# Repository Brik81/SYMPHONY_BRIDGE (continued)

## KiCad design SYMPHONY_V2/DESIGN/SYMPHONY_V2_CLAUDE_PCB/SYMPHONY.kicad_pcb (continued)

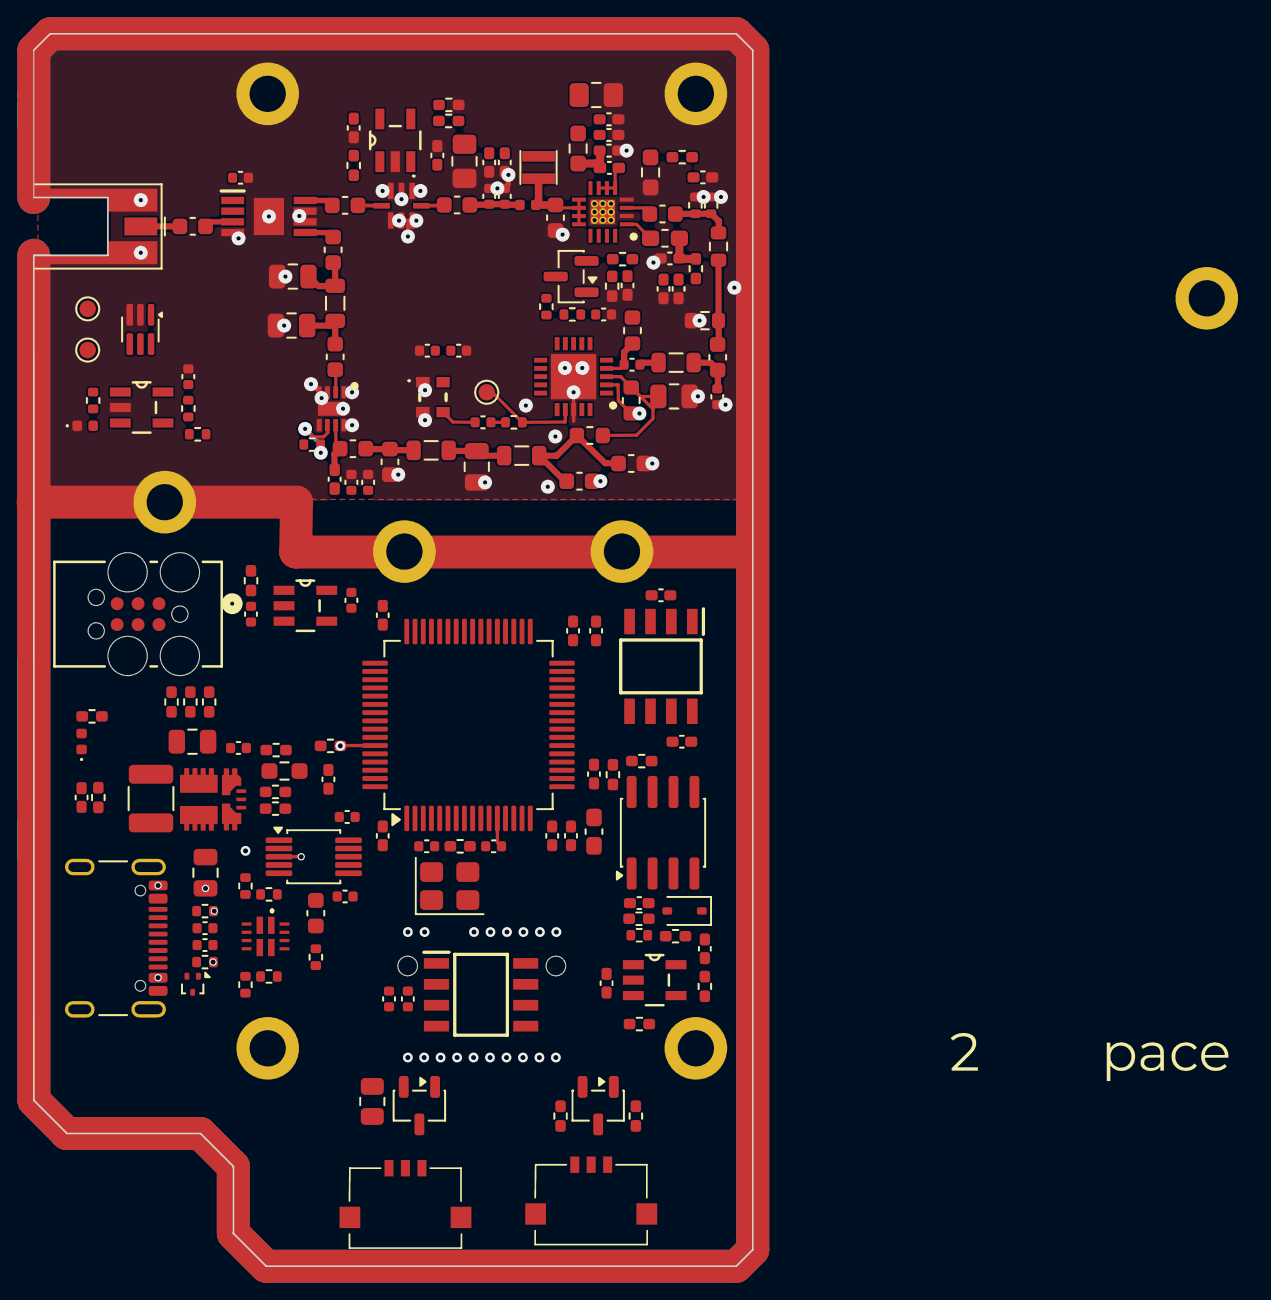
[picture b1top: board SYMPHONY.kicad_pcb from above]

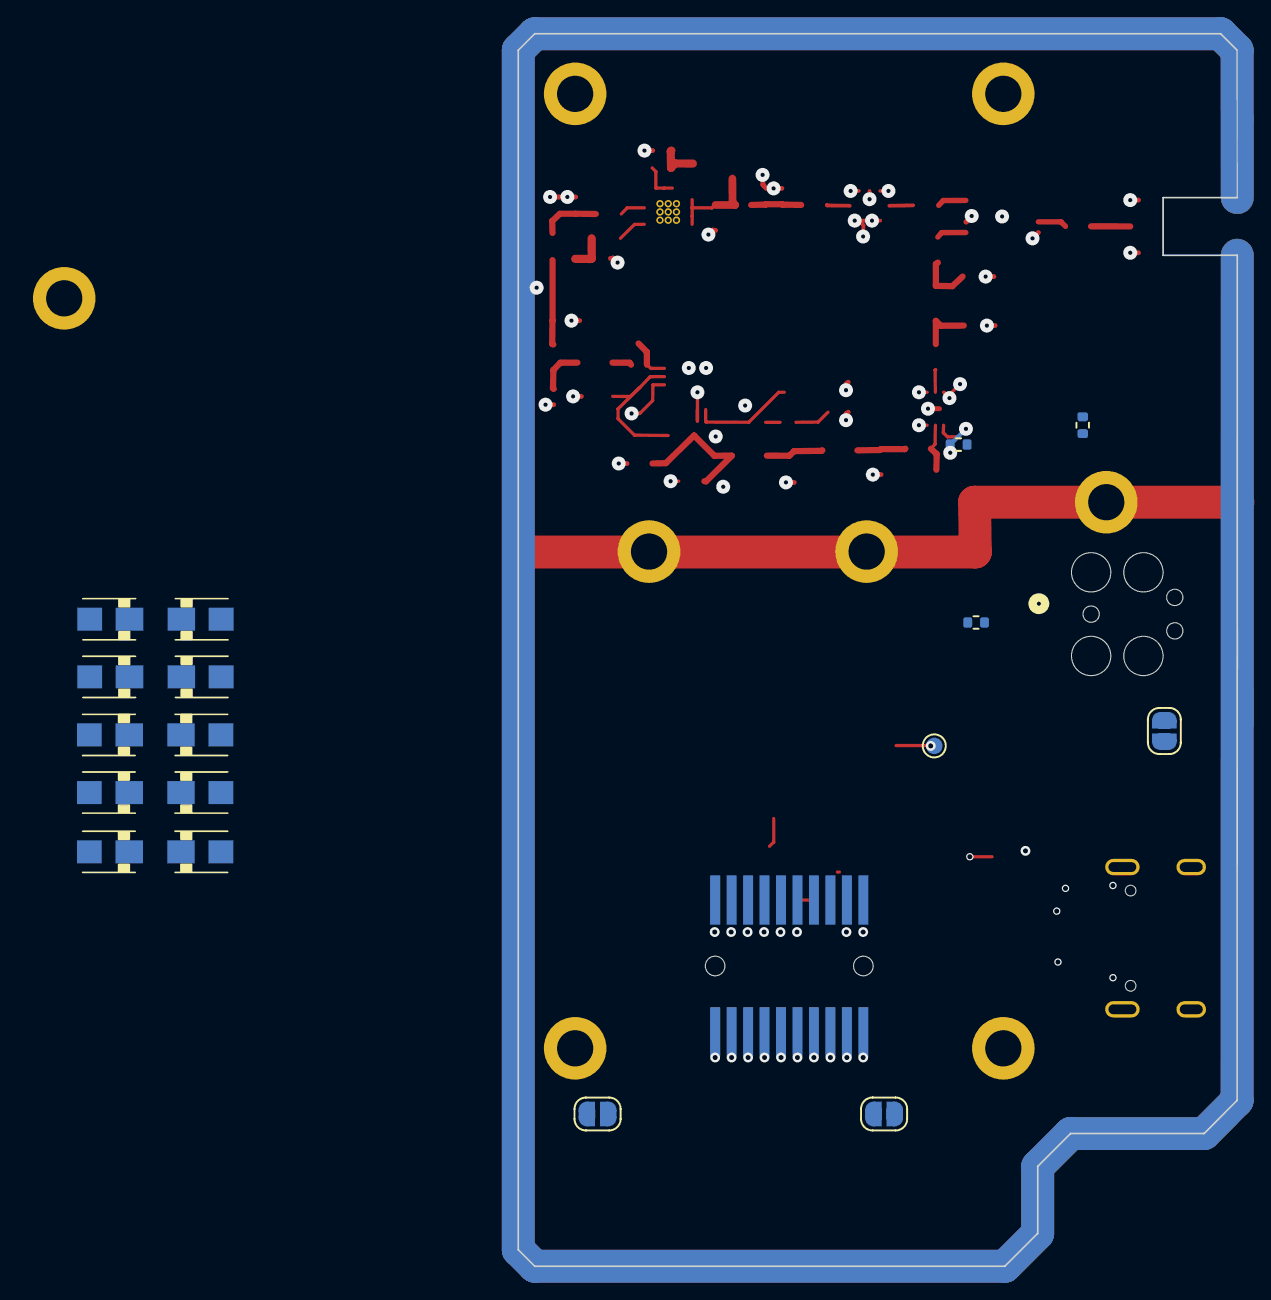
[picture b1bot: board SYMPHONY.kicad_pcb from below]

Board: 8 copper layers, 43.7 x 74.8 mm, 193 parts (18 on the bottom side), 108 nets.

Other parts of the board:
C419, C424: CPH3225A

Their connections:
GND: C419.2 (-), C424.2 (-); also elsewhere on the board
RTC_VBAT: C419.1 (+), C424.1 (+); also elsewhere on the board

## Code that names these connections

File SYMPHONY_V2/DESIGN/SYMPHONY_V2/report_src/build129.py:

import pathlib
d = pathlib.Path(__file__).parent
p = d / 'symphony_version_log.html'
h = p.read_text(encoding='utf8')

def sub1(o, rep):
    global h
    assert h.count(o) == 1, o[:60]
    h = h.replace(o, rep)


sub1('symphony_version_log · rev. 1.28"', 'symphony_version_log · rev. 1.29"')
sub1("<div><b>1.28</b> del 30/10/2026",
     "<div><b>1.29</b> del 02/11/2026 – R-04 chiuso senza modifiche allo schema: limite di potenza e sequenza TX affidati al firmware; raccolta delle note per il firmware (§41)</div><div>1.28 del 30/10/2026")
sub1('tr.r128 td {', 'tr.r129 td { background: #edf2e6 !important; }\ntr.r128 td {')
sub1('<li><a href="#partAA">Parte AA – Rev. 1.28: condensatori RF GQM1875 0603 (R-10) e decisione su J15 (R-09)</a></li>',
     '<li><a href="#partAA">Parte AA – Rev. 1.28: condensatori RF GQM1875 0603 (R-10) e decisione su J15 (R-09)</a></li>\n'
     '<li><a href="#partAB">Parte AB – Rev. 1.29: potenza TX (R-04) e note per il firmware</a></li>')
sub1('cipria</span> = rev. 1.28,',
     'cipria</span> = rev. 1.28, righe <span style="background:#edf2e6;padding:0 2mm">salvia</span> = rev. 1.29,')

REV = ('<tr class="r129"><td>1.29</td><td>problema R-04 della revisione indipendente del 27/10/2026<br>decisione di Brik81 del 02/11, registrata da Claude Code</td>'
       '<td>Nessuna modifica allo schema. Il limite della potenza in uscita (≤ 31 dBm all\'antenna) e la sequenza di trasmissione sono requisiti del firmware; misura obbligatoria sul prototipo; R242/R243 restano come regolazione della VAPC. Aggiunta la raccolta delle note per il firmware (§41)</td>'
       '<td>Claude Code</td><td><b>Brik81</b></td>'
       '<td>"si se l\'hw è corretto andiamo di A e lasciamo scritto al firmwarsita" (02/11)</td></tr>\n')
i = h.find('<h2>Registro revisioni</h2>'); j = h.find('</table>', i); h = h[:j] + REV + h[j:]
sub1('Rev. 1.28: <code>UHF.kicad_sch</code>',
     'Rev. 1.29: nessun file di progetto modificato. Rev. 1.28: <code>UHF.kicad_sch</code>')

rows = ('<tr class="r129"><td>1.29-01</td><td>UHF</td><td>Catena TX (IC204 → pad → IC2 → FL201 → IC202)</td>'
        '<td>Con il Si4464 a +20 dBm il PA è in saturazione profonda (≈ +9 dBm in ingresso, ne bastano ≈ −9). Al commutatore arrivano ≈ 32,5 dBm, contro un massimo assoluto dell\'HMC349 di 33,5 dBm (30 dBm in hot switching); l\'LFCG-490+ a 85 °C regge ≈ 1,9 W</td>'
        '<td>Nessuna modifica all\'hardware. Requisiti firmware F-01 e F-02 (§41) e misura M-01 sul prototipo. Se Pout supera i 31 dBm anche con il limite firmware, si ritoccano R242/R243</td>'
        '<td>R-04, §41</td><td>Brik81 · 02/11</td><td>—</td></tr>\n')
i = h.find('<h2>Registro modifiche</h2>'); j = h.find('</table>', i); h = h[:j] + rows + h[j:]

PART = """
<section class="part" id="partAB">
<div class="partlabel">Parte AB</div>
<h1 class="parttitle">Rev. 1.29 – Potenza TX (R-04) e note per il firmware</h1>
</section>
<h2 id="s41">41. R-04 e raccolta delle note per il firmware</h2>
<p><b>R-04.</b> L'hardware della catena TX è corretto. Il PA è protetto in ingresso: anche con il Si4464 al massimo arrivano ≈ +9 dBm, contro un massimo assoluto di +13 dBm. Il margine che manca è a valle, sul commutatore e sul filtro. Un pad più grande non risolverebbe, perché in saturazione la potenza in uscita resta circa la Psat qualunque sia il pilotaggio. Le leve vere sono il pilotaggio, cioè PA_PWR_LVL (sotto la compressione il PA è lineare), e la VAPC (partitore R242/R243). Brik81 ha scelto di non modificare lo schema e di affidare il limite al firmware. Con modulazione FSK/GFSK lavorare vicino alla saturazione va bene, perché l'inviluppo è costante.</p>
<p><b>Come è fatto l'hardware.</b> Un solo pin, PC2 (rete UHF.EN_TX_ANT_SW), comanda insieme tre cose: il CTRL dell'HMC349, l'abilitazione dell'APC del PA (Q701 P-MOS con pull-up R702 verso 3V3, gate tramite R703: PC2 basso = APC alimentata) e, tramite l'invertitore U701, EN_RX_LNA. Con PC2 in alta impedenza (boot, reset dell'MCU) il pull-up tiene il PA spento. Il commutatore e l'APC si muovono quindi insieme. La RF però c'è solo quando il Si4464 trasmette: per non commutare mai con la RF presente basta cambiare PC2 solo quando il Si4464 non è in TX.</p>
<div class="box">
<p><b>Note per il firmware: requisiti hardware da rispettare</b> (raccolta di quelle sparse nelle revisioni precedenti, più le nuove di R-04)</p>
<table>
<tr><th>ID</th><th>Argomento</th><th>Requisito</th><th>Origine</th></tr>
<tr><td><b>F-01</b></td><td>Potenza TX</td><td><b>Limite rigido</b> su PA_PWR_LVL del Si4464, tarato sul prototipo (misura M-01) per avere <b>≤ 31 dBm</b> all'uscita d'antenna. Il valore va scritto come costante non modificabile da telecomando, o al più con una saturazione lato firmware. Il Si4464 non deve mai andare a +20 dBm</td><td>R-04 (rev 1.29), §3, S-07</td></tr>
<tr><td><b>F-02</b></td><td>Sequenza TX/RX</td><td>Entrata in TX: Si4464 non in TX → PC2 su "TX" (commutatore su TX, APC del PA alimentata, LNA spento) → attendere che commutatore e PA si assestino → Si4464 START_TX. Uscita: fine pacchetto, Si4464 fuori da TX (READY/RX) → solo dopo PC2 su "RX". <b>Mai cambiare PC2 mentre il Si4464 trasmette</b> (hot switching dell'HMC349, limite 30 dBm)</td><td>R-04 (rev 1.29), §4, 1.1-04</td></tr>
<tr><td><b>F-03</b></td><td>Durata TX</td><td>Preferire trasmissioni a impulsi o con duty cycle limitato. L242 (NRS2012, 1,7 A ΔT 40 °C) e l'LFCG-490+ (≈ 1,9 W a 85 °C) scaldano in trasmissione continua alla massima potenza. Se serve TX continuo, ridurre F-01</td><td>rev 1.25, R-04</td></tr>
<tr><td><b>F-04</b></td><td>Clock del Si4464</td><td>POWER_UP con l'opzione TCXO (TCXO a 32 MHz su XIN, XOUT flottante) e banco capacità XO (GLOBAL_XO_TUNE) = 0</td><td>§2</td></tr>
<tr><td><b>F-05</b></td><td>Reset del Si4464</td><td>PC4 (RF_MR_N) basso = reset della radio. Dopo il rilascio di ~MR o all'accensione aspettare almeno 200 ms (ritardo del supervisore IC205) più il POR del Si4464 prima di mandare comandi SPI, e controllare CTS</td><td>supervisore IC205</td></tr>
<tr><td><b>F-06</b></td><td>Clock dell'MCU</td><td>HSE_VALUE = 24000000 (quarzo Y1 da 24 MHz). Con un valore diverso UART, USB e timer partono alla frequenza sbagliata</td><td>S-04, rev 1.15</td></tr>
<tr><td><b>F-07</b></td><td>Console</td><td>USART1 su PA9/PA10 (AF7), collegata al CH340 U402, non UART4. Bootloader: BOOT0 (PH3, TP1) alto al reset, poi STM32CubeProgrammer in UART</td><td>rev 1.8</td></tr>
<tr><td><b>F-08</b></td><td>Sensori di temperatura</td><td>ADC1 canale 16 (PB1, V_TEMP_PA) e canale 2 (PC1, V_TEMP_BUCK), misura raziometrica su VDDA = 3V3. Calibrazione a un punto per canale (offset del TLV9051 ≈ ±0,9 °C)</td><td>S-06, rev 1.17–1.18, R-18</td></tr>
<tr><td><b>F-09</b></td><td>RTC DS3231M</td><td>All'avvio EN32KHZ = 0 (registro 0Fh, bit 3): l'uscita 32 kHz non è usata e consuma il backup. Dopo un'interruzione lunga controllare il flag OSF e risincronizzare l'ora</td><td>S-09, rev 1.20</td></tr>
</table>
<p><b>Misure obbligatorie sul prototipo.</b> <b>M-01:</b> Pout all'uscita d'antenna su carico da 50 Ω (attenuatore di potenza), alla temperatura ambiente e se possibile a caldo, con il Si4464 al valore F-01 e al massimo. Se con il valore F-01 si superano i 31 dBm, ridurre la VAPC con R242/R243. <b>M-02:</b> adattamento d'uscita del PA (S22 o potenza in banda 430–440 MHz) con L242 = NRS2012 e C260 = 27 pF (rev 1.25).</p>
</div>
<p>Dati non verificati sul datasheet: guadagno ≈ 42 dB e P3dB ≈ 34 dBm (riepilogo EVB Qorvo del 30/06/2025, alla tensione della EVB); la curva Pout/VAPC del QPA9510. Per questo il valore di F-01 si fissa con la misura M-01 e non con un calcolo.</p>
"""
sub1('\n</body></html>', PART + '\n</body></html>')
p.write_text(h, encoding='utf8')
print('ok')

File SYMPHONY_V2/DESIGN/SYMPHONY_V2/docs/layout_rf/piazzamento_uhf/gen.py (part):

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            ("IC2", "IC2 QPA9510 (PA) \\textendash{} rotazione 180\\textdegree", 7.0),
            ("Q201", "Q201 TQP3M9036 (LNA) \\textendash{} rotazione 0\\textdegree", 9.0),
            ("FL201", "FL201 LFCG-490+ \\textendash{} rotazione 180\\textdegree", 9.0)]
    short = {"RF_SW_COM": "RFC (antenna)", "RF_SW_TX": "RF2 = TX", "RF_SW_RX": "RF1 = RX", "UHF.EN_TX_ANT_SW": "CTRL (PC2)",
             "5V0": "VDD 5V0", "RF_RX_P": "RXP", "RF_RX_N": "RXN", "RF_SI_TX": "TX", "RF_SDN": "SDN", "RF_XIN": "XIN",
             "SPI1.CLK": "SCK", "SPI1.MISO": "MISO", "SPI1.MOSI": "MOSI", "SPI1.CS": "NSEL", "UHF.RF_IRQ": "nIRQ",
             "RF_PA_IN": "RF IN", "RF_PA_OUT": "RF OUT", "PA_VCC1": "VCC1", "PA_VCC2": "VCC2", "Net-(IC2-APC1)": "APC",
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
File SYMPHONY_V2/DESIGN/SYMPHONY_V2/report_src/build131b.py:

import pathlib
p = pathlib.Path(__file__).parent / 'symphony_version_log.html'
h = p.read_text(encoding='utf8')

def sub1(o, rep):
    global h
    assert h.count(o) == 1, o[:60]
    h = h.replace(o, rep)

sub1("<p><b>Ancora aperto in R-12:</b> GPIO_PPS (pin 17), GPIOSX_0 (pin 14) e GPIOSX_2 (pin 13) non sono collegati all'MCU. Brik81 deve decidere se lasciarli così o collegare il PPS a un ingresso timer/EXTI per la sincronizzazione del tempo.</p>",
     "<p><b>Aggiornamento 02/11 – R-12 chiuso.</b> Anche GPIO_PPS (pin 17), GPIOSX_0 (pin 14) e GPIOSX_2 (pin 13) restano non collegati per decisione di Brik81: \"nono lascia stare se non è connessa fregatenene, sono li per avere nomi standard essendo per noi un connettore standard\". Le etichette servono solo a mantenere i nomi standard del connettore.</p>")
sub1("<td>R-12, §43</td><td>Brik81 · 02/11</td><td>Claude Code · 02/11</td></tr>",
     "<td>R-12, §43</td><td>Brik81 · 02/11</td><td>Claude Code · 02/11</td></tr>\n"
     "<tr class=\"r131\"><td>1.31-02</td><td>IF</td><td>J708 pin 13 GPIOSX_2, 14 GPIOSX_0, 17 GPIO_PPS</td>"
     "<td>Etichette senza collegamento all'MCU</td><td>Nessuna modifica: restano solo per i nomi standard del connettore. R-12 chiuso</td>"
     "<td>R-12, §43</td><td>Brik81 · 02/11</td><td>—</td></tr>")
p.write_text(h, encoding='utf8')
print('ok')
